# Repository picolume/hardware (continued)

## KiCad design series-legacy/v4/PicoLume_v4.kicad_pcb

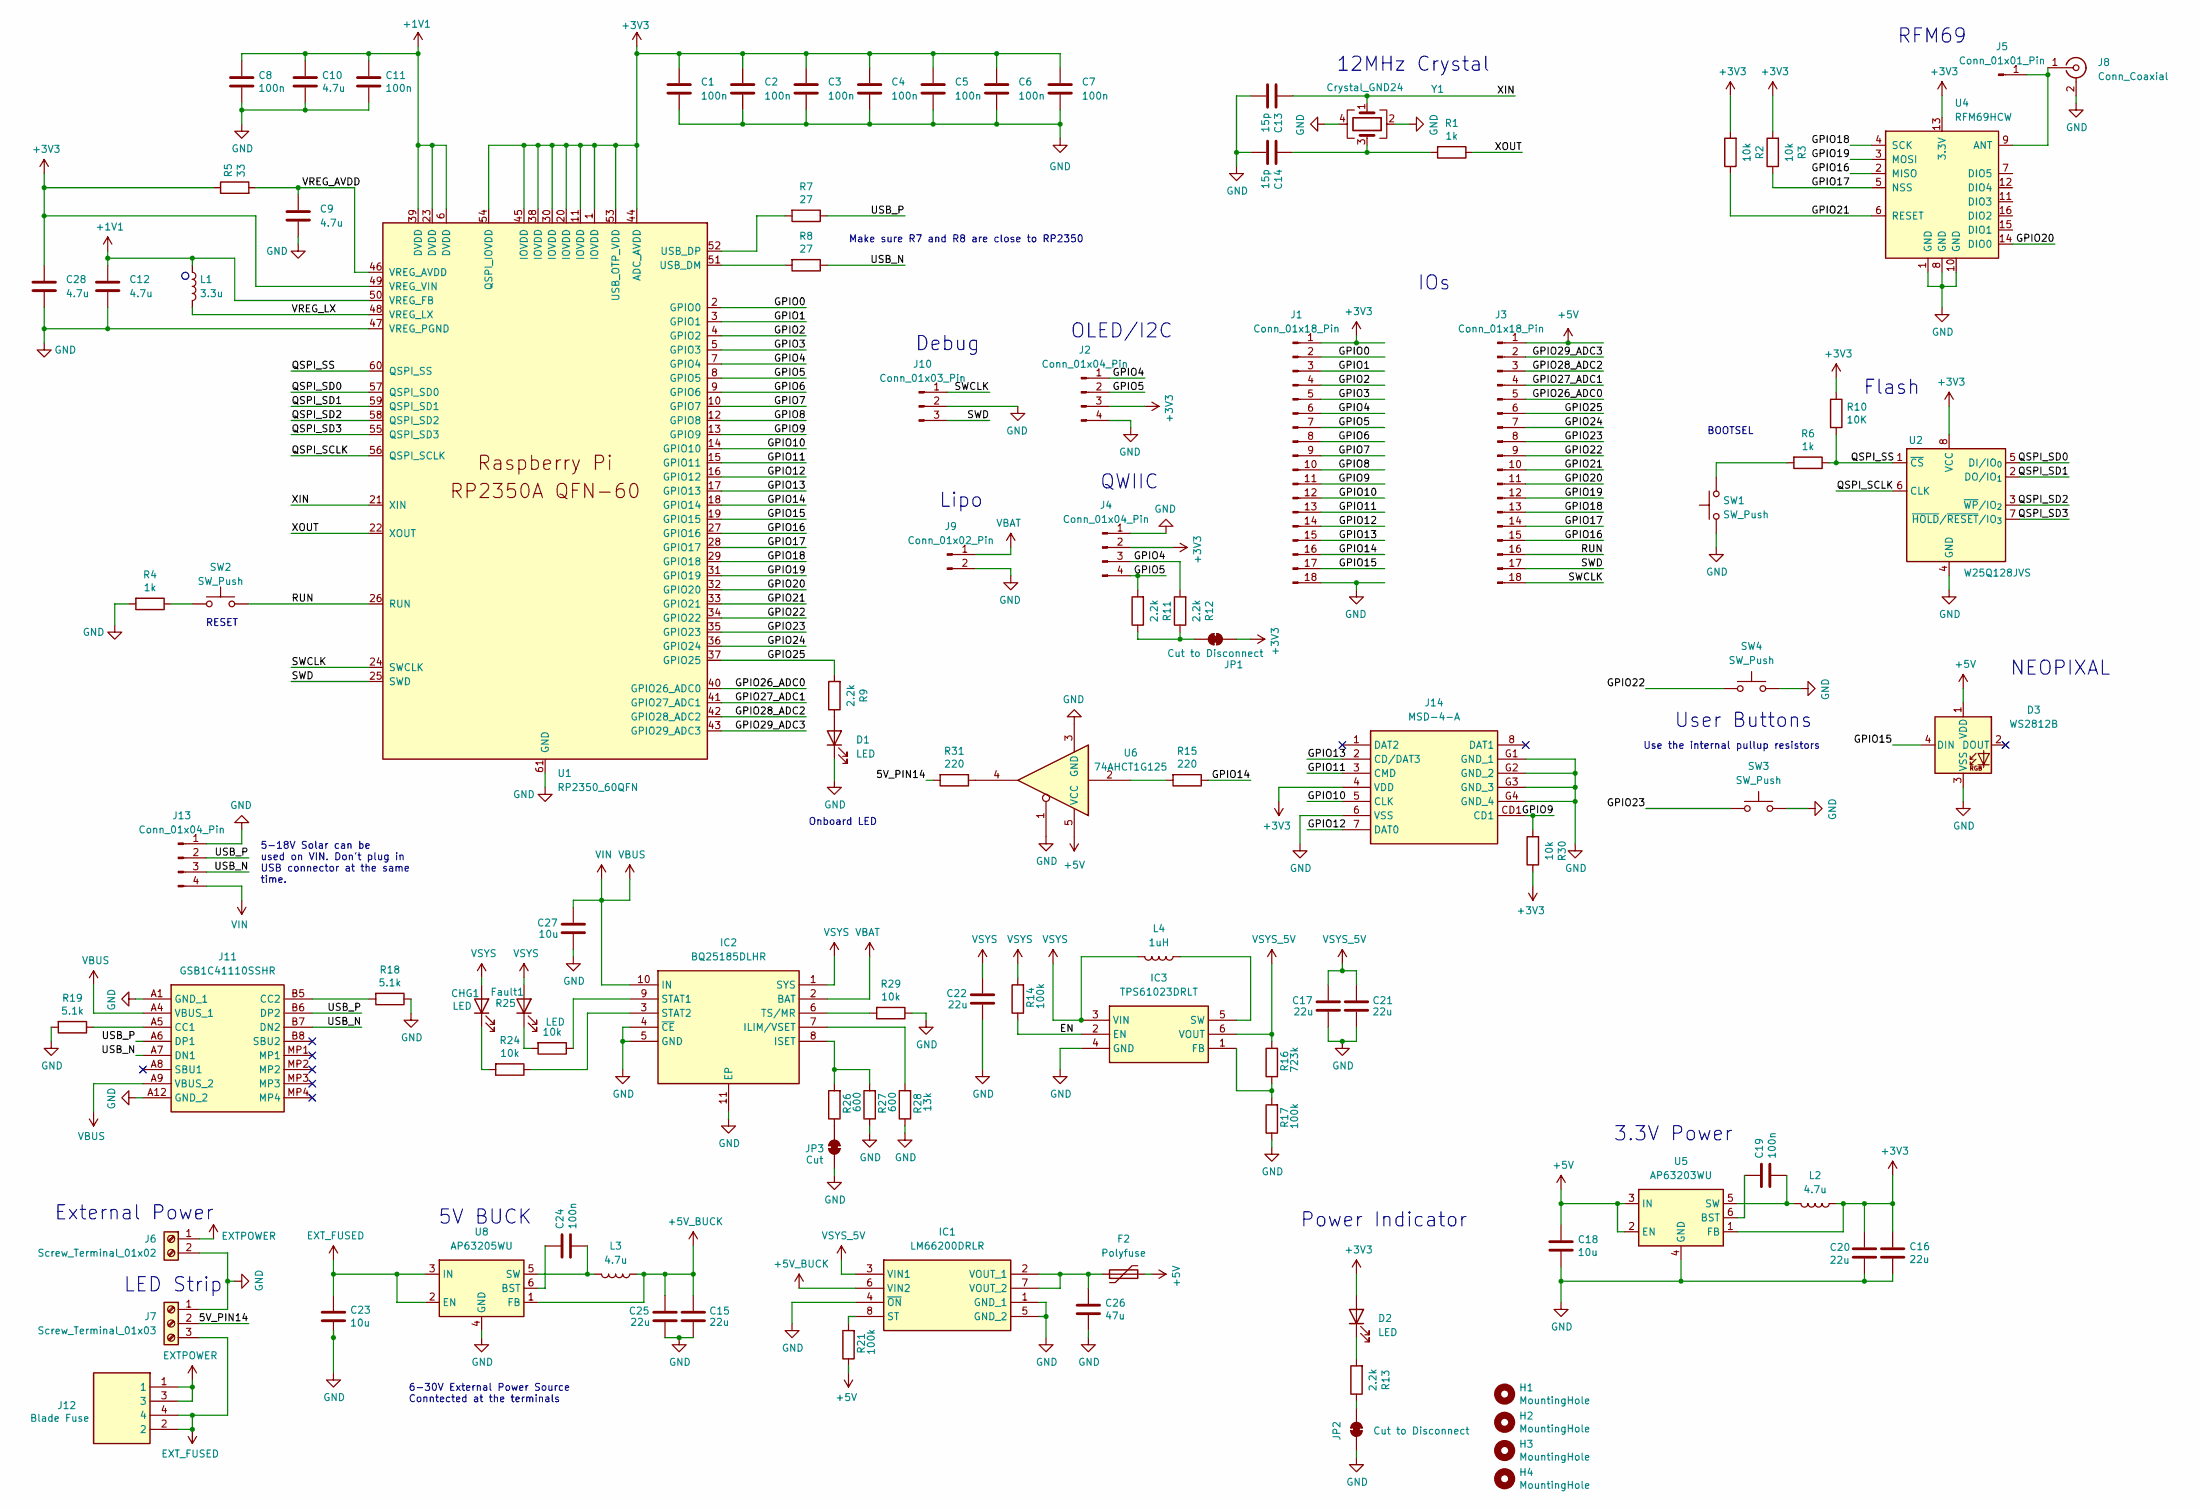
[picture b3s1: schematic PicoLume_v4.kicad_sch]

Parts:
C1, C2, C3, C4, C5, C6, C7, C8, C11, C19, C24: 100n; C_0603_1608Metric
C9, C10, C12, C28: 4.7u; C_0603_1608Metric
C13, C14: 15p; C_0603_1608Metric
C15, C16, C17, C20, C21, C22, C25: 22u; C_0805_2012Metric
C18: 10u; C_0805_2012Metric
C23: 10u; C_1206_3216Metric
C26: 47u; C_1206_3216Metric
C27: 10u; C_0603_1608Metric
CHG1: LED; LED_0603_1608Metric
D1, D2: LED; LED_0603_1608Metric
D3: WS2812B; INPI15TAT5R5G5B
F2: Polyfuse; 1206L075132WR
Fault1: LED; LED_0603_1608Metric
H1, H2, H3, H4: MountingHole; MountingHole_3.2mm_M3
IC1: LM66200DRLR; SOTFL50P160X60-8N; Mouser Part Number 595-LM66200DRLR
IC2: BQ25185DLHR; SON40P220X200X80-11N; Mouser Part Number 595-BQ25185DLHR
IC3: TPS61023DRLT; SOTFL50P160X60-6N; Mouser Part Number 595-TPS61023DRLT
J1, J3: Conn_01x18_Pin; PinHeader_1x18_P2.54mm_Vertical
J2, J13: Conn_01x04_Pin; PinHeader_1x04_P2.54mm_Vertical
J4: Conn_01x04_Pin; JST_SH_SM04B-SRSS-TB_1x04-1MP_P1.00mm_Horizontal
J5: Conn_01x01_Pin; PinHeader_1x01_P2.54mm_Vertical
J6: Screw_Terminal_01x02; TerminalBlock_bornier-2_P5.08mm
J7: Screw_Terminal_01x03; TerminalBlock_bornier-3_P5.08mm
J8: Conn_Coaxial; U.FL_Molex_MCRF_73412-0110_Vertical
J9: Conn_01x02_Pin; JST_PH_S2B-PH-K_1x02_P2.00mm_Horizontal
J10: Conn_01x03_Pin; JST_SH_BM03B-SRSS-TB_1x03-1MP_P1.00mm_Vertical
J11: GSB1C41110SSHR; Manufacturer_Part_Number GSB1C41110SSHR
J12: Blade Fuse; 35222; Mouser Part Number 534-3522-2
J14: MSD-4-A; MSD4A; Mouser Part Number 179-MSD-4-A
JP1, JP2: Cut to Disconnect; SolderJumper-2_P1.3mm_Bridged_RoundedPad1.0x1.5mm
JP3: Cut; SolderJumper-2_P1.3mm_Bridged_RoundedPad1.0x1.5mm
L1: 3.3u; AOTAB201610S3R3101T
L2, L3: 4.7u; L_1210_3225Metric
L4: 1uH; L_1210_3225Metric
R1, R4, R6: 1k; R_0603_1608Metric
R2, R3, R24, R25, R29, R30: 10k; R_0603_1608Metric
R5: 33; R_0603_1608Metric
R7, R8: 27; R_0603_1608Metric
R9, R11, R12, R13: 2.2k; R_0603_1608Metric
R10: 10K; R_0603_1608Metric
R14, R17, R21: 100k; R_0603_1608Metric
R15, R31: 220; R_0603_1608Metric
R16: 723k; R_0603_1608Metric
R18, R19: 5.1k; R_0603_1608Metric
R26, R27: 600; R_0603_1608Metric
R28: 13k; R_0603_1608Metric
SW1, SW2, SW3, SW4: SW_Push; FSMH
U1: RP2350_60QFN; RP2350-QFN-60-1EP_7x7_P0.4mm_EP3.4x3.4mm_ThermalVias
U2: W25Q128JVS; SOIC-8_5.3x5.3mm_P1.27mm
U4: RFM69HCW; MOD_COM-13909
U5: AP63203WU; TSOT-23-6
U6: 74AHCT1G125; SOT-25
U8: AP63205WU; TSOT-23-6
Y1: Crystal_GND24; ABM8272T3

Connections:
+1V1: C8.1, C10.1, C11.1, C12.1, L1.1, U1.6 (DVDD), U1.23 (DVDD), U1.39 (DVDD), U1.50 (VREG_FB)
+3V3: C1.1, C2.1, C3.1, C4.1, C5.1, C6.1, C7.1, C16.1, C20.1, C28.1, D2.2 (A), J1.1, J2.3, J4.2, J14.4 (VDD), JP1.2 (B), L2.1, R2.2, R3.2, R5.1, R10.1, R30.1, U1.1 (IOVDD), U1.11 (IOVDD), U1.20 (IOVDD), U1.30 (IOVDD), U1.38 (IOVDD), U1.44 (ADC_AVDD), U1.45 (IOVDD), U1.49 (VREG_VIN), U1.53 (USB_OTP_VDD), U1.54 (QSPI_IOVDD), U2.8 (VCC), U4.13 (3.3V), U5.1 (FB); also elsewhere on the board
+5V: C18.1, D3.1 (VDD), F2.2, J3.1, R21.1, U5.2 (EN), U5.3 (IN), U6.5 (VCC)
+5V_BUCK: C15.1, C25.1, IC1.6 (VIN2), L3.1, U8.1 (FB)
/5V_PIN14: J7.2, R31.2
/EN: IC3.2 (EN), R14.1
/GPIO0: J1.2, U1.2 (GPIO0)
/GPIO1: J1.3, U1.3 (GPIO1)
/GPIO2: J1.4, U1.4 (GPIO2)
/GPIO3: J1.5, U1.5 (GPIO3)
/GPIO4: J1.6, J2.1, J4.3, R12.2, U1.7 (GPIO4); also elsewhere on the board
/GPIO5: J1.7, J2.2, J4.4, R11.2, U1.8 (GPIO5); also elsewhere on the board
/GPIO6: J1.8, U1.9 (GPIO6)
/GPIO7: J1.9, U1.10 (GPIO7)
/GPIO8: J1.10, U1.12 (GPIO8)
/GPIO9: J1.11, J14.CD1, R30.2, U1.13 (GPIO9)
/GPIO10: J1.12, J14.5 (CLK), U1.14 (GPIO10)
/GPIO11: J1.13, J14.3 (CMD), U1.15 (GPIO11)
/GPIO12: J1.14, J14.7 (DAT0), U1.16 (GPIO12)
/GPIO13: J1.15, J14.2 (CD/DAT3), U1.17 (GPIO13)
/GPIO14: J1.16, R15.1, U1.18 (GPIO14)
/GPIO15: D3.4 (DIN), J1.17, U1.19 (GPIO15)
/GPIO16: J3.15, U1.27 (GPIO16), U4.2 (MISO)
/GPIO17: J3.14, R3.1, U1.28 (GPIO17), U4.5 (NSS); also elsewhere on the board
/GPIO18: J3.13, U1.29 (GPIO18), U4.4 (SCK)
/GPIO19: J3.12, U1.31 (GPIO19), U4.3 (MOSI)
/GPIO20: J3.11, U1.32 (GPIO20), U4.14 (DIO0)
/GPIO21: J3.10, R2.1, U1.33 (GPIO21), U4.6 (RESET); also elsewhere on the board
/GPIO22: J3.9, SW4.2, U1.34 (GPIO22)
/GPIO23: J3.8, SW3.2, U1.35 (GPIO23)
/GPIO24: J3.7, U1.36 (GPIO24)
/GPIO25: J3.6, R9.2, U1.37 (GPIO25)
/GPIO26_ADC0: J3.5, U1.40 (GPIO26_ADC0)
/GPIO27_ADC1: J3.4, U1.41 (GPIO27_ADC1)
/GPIO28_ADC2: J3.3, U1.42 (GPIO28_ADC2)
/GPIO29_ADC3: J3.2, U1.43 (GPIO29_ADC3)
/QSPI_SCLK: U1.56 (QSPI_SCLK), U2.6 (CLK)
/QSPI_SD0: U1.57 (QSPI_SD0), U2.5 (DI/IO_{0})
/QSPI_SD1: U1.59 (QSPI_SD1), U2.2 (DO/IO_{1})
/QSPI_SD2: U1.58 (QSPI_SD2), U2.3 (~WP/IO_{2})
/QSPI_SD3: U1.55 (QSPI_SD3), U2.7 (~HOLD/~RESET/IO_{3})
/QSPI_SS: R6.1, R10.2, U1.60 (QSPI_SS), U2.1 (~CS)
/RUN: J3.16, SW2.2, U1.26 (RUN)
/SWCLK: J3.18, J10.1, U1.24 (SWCLK)
/SWD: J3.17, J10.3, U1.25 (SWD)
/USB_N: J11.A7 (DN1), J11.B7 (DN2), J13.3, R8.1
/USB_P: J11.A6 (DP1), J11.B6 (DP2), J13.2, R7.1
/VREG_AVDD: C9.1, R5.2, U1.46 (VREG_AVDD)
/VREG_LX: L1.2, U1.48 (VREG_LX)
/XIN: C13.1, U1.21 (XIN), Y1.1
/XOUT: R1.1, U1.22 (XOUT)
EXTPOWER: J6.1, J12.1, J12.3
EXT_FUSED: C23.1, J7.3, J12.2, J12.4, U8.2 (EN), U8.3 (IN)
GND: C1.2, C2.2, C3.2, C4.2, C5.2, C6.2, C7.2, C8.2, C9.2, C10.2, C11.2, C12.2, C13.2, C14.2, C15.2, C16.2, C17.2, C18.2, C20.2, C21.2, C22.2, C23.2, C25.2, C26.2, C27.2, C28.2, D1.1 (K), D3.3 (VSS), IC1.1 (GND_1), IC1.4 (~ON), IC1.5 (GND_2), IC2.4 (~CE), IC2.5 (GND), IC2.11 (EP), IC3.4 (GND), J1.18, J2.4, J4.1, J6.2, J7.1, J8.2 (Ext), J9.2, J10.2, J11.A1 (GND_1), J11.A12 (GND_2), J13.1, J14.6 (VSS), J14.G1 (GND_1), J14.G2 (GND_2), J14.G3 (GND_3), J14.G4 (GND_4), JP2.2 (B), JP3.2 (B), R4.2, R17.1, R18.1, R19.2, R27.1, R28.1, R29.1, SW1.1, SW3.1, SW4.1, U1.47 (VREG_PGND), U1.61 (GND), U2.4 (GND), U4.1 (GND), U4.8 (GND), U4.10 (GND), U5.4 (GND), U6.1, U6.3 (GND), U8.4 (GND), Y1.2, Y1.4
unnamed: C14.1, R1.2, Y1.3
unnamed: CHG1.1 (K), R24.2
unnamed: D1.2 (A), R9.1
unnamed: D2.1 (K), R13.2
unnamed: Fault1.1 (K), R25.2
unnamed: IC1.8 (ST), R21.2
unnamed: C26.1, F2.1, IC1.2 (VOUT_1), IC1.7 (VOUT_2)
unnamed: IC2.7 (ILIM/VSET), R28.2
unnamed: IC2.8 (ISET), R26.2, R27.2
unnamed: IC2.9 (STAT1), R25.1
unnamed: IC2.3 (STAT2), R24.1
unnamed: IC2.6 (TS/MR), R29.2
unnamed: IC3.1 (FB), R16.1, R17.2
unnamed: IC3.5 (SW), L4.1
unnamed: J5.1, J8.1 (In), U4.9 (ANT)
unnamed: J11.A5 (CC1), R19.1
unnamed: J11.B5 (CC2), R18.2
unnamed 71: JP1.1 (A), R11.1, R12.1; also elsewhere on the board
unnamed: JP2.1 (A), R13.1
unnamed: JP3.1 (A), R26.1
unnamed: R4.1, SW2.1
unnamed: R6.2, SW1.2
unnamed: R15.2, U6.2
unnamed: R31.1, U6.4
unnamed: R8.2, U1.51 (USB_DM)
unnamed: R7.2, U1.52 (USB_DP)
unnamed: C19.1, U5.6 (BST)
unnamed: C19.2, L2.2, U5.5 (SW)
unnamed: C24.1, U8.6 (BST)
unnamed: C24.2, L3.2, U8.5 (SW)
VBAT: IC2.2 (BAT), J9.1
VBUS: C27.1, IC2.10 (IN), J11.A4 (VBUS_1), J11.A9 (VBUS_2), J13.4
VSYS: C22.1, CHG1.2 (A), Fault1.2 (A), IC2.1 (SYS), IC3.3 (VIN), L4.2, R14.2
VSYS_5V: C17.1, C21.1, IC1.3 (VIN1), IC3.6 (VOUT), R16.2

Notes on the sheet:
Flash
Power Indicator
Lipo
5V BUCK
Make sure R7 and R8 are close to RP2350
12MHz Crystal
Onboard LED
Debug
RFM69
6-30V External Power Source Conntected at the terminals
QWIIC
NEOPIXAL
RESET
LED Strip
User Buttons
External Power
5-18V Solar can be used on VIN. Don't plug in USB connector at the same time.
OLED/I2C
IOs
Use the internal pullup resistors
BOOTSEL
3.3V Power

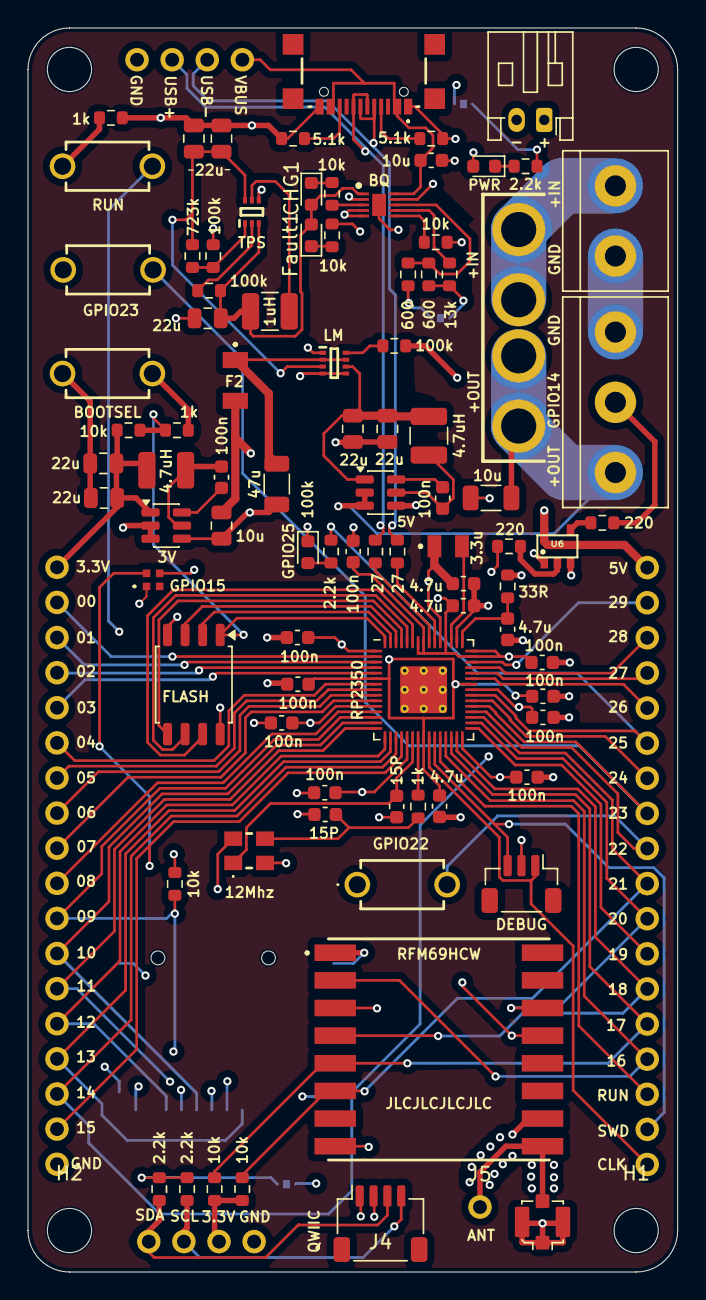
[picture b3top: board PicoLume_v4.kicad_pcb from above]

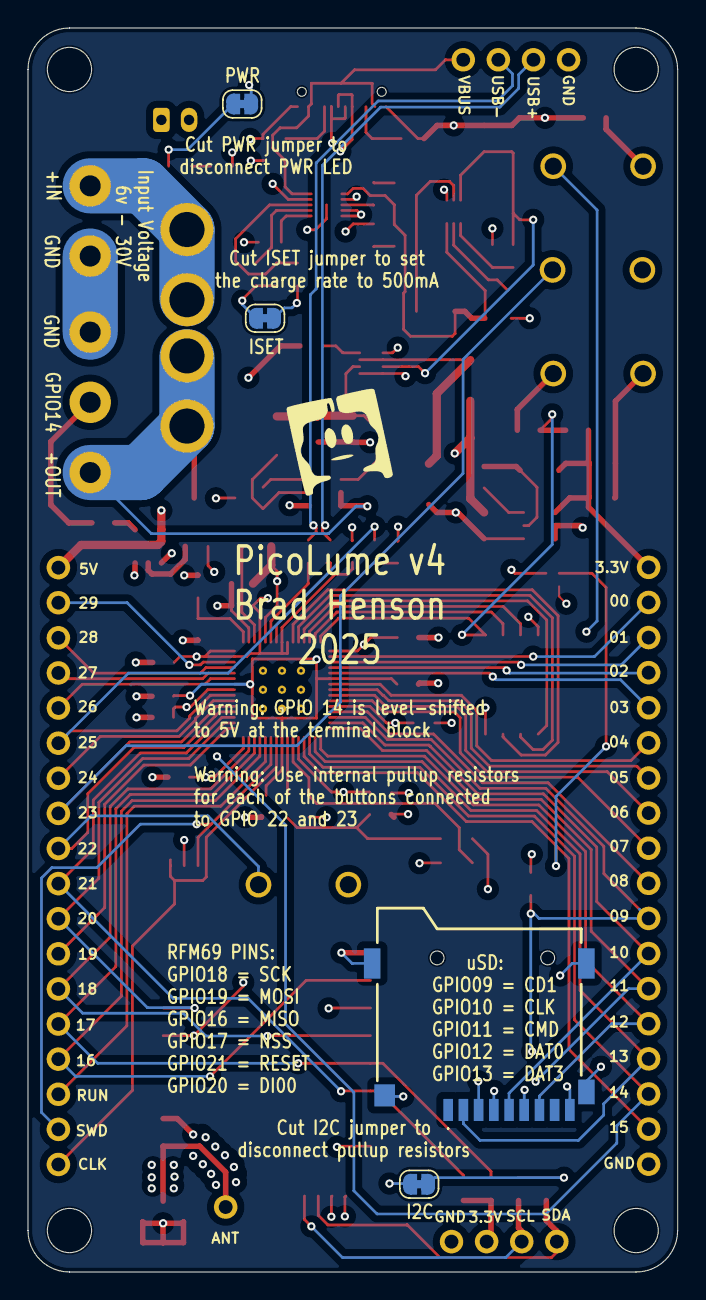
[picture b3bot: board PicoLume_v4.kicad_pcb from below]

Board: 4 copper layers, 47.0 x 90.0 mm, 101 parts (4 on the bottom side), 88 nets.

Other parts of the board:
2.2k, 2.2k#2: 2.2k; R_0603_1608Metric
10k, 10k#2: 10k; R_0603_1608Metric

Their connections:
+3V3: 10k.2, 10k#2.2; also elsewhere on the board
/GPIO4: 2.2k.2; also elsewhere on the board
/GPIO5: 2.2k#2.2; also elsewhere on the board
/GPIO17: 10k.1; also elsewhere on the board
/GPIO21: 10k#2.1; also elsewhere on the board
unnamed 71: 2.2k.1, 2.2k#2.1; also elsewhere on the board

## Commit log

2025-12-16 Initial commit: PicoLume Hardware KiCad projects
    Includes:
    - series-legacy: v1-v4 board designs
    - series-prop: receiver-v1 design
    - series-mini: placeholder for future designs
2025-12-17 Add MIT License to the project
2025-12-18 Updated readme file
2025-12-18 Removed bulk output cap and added PTC on VBAT input
2025-12-19 deleted empty folder for undeveloped board
2025-12-19 removed reference to the mini board
2025-12-20 updated gitignore file
2025-12-23 replaced the RGB led with a button on GPIO15
2025-12-23 renamed prop receiver from v1 to v0.1.0
2025-12-24 added remote design files
2025-12-24 auto save
